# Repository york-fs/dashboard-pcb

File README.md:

# York FS Dashboard 
An embedded dashboard built around an STM32F103XX microcontroller with a 1920x480 LCD DWIN display for driver interaction and real time system status

## Features
- **Display**
  - 1920x480 DWIN TFT (https://www.dwin-global.com/8-88-inch-uart-smart-lcm-model-dmg19480c088_03w-product/)
  - Used for system feedback and driver information  
- **Controls**
  - 3-position illuminated rocker switch for *Ready to Drive* control  
- **Indicators**
  - 4 × 1 W high-power LEDs with dedicated PWM drivers  
  - Functions:  
    - IMD (Insulation Monitoring Device)  
    - BMS (Battery Management System)  
    - Ready to Drive  
    - TSAL (Traction System Active Light)  
- **Communication**
  - Integrated CAN transceiver  

## PCB Notes
- Designed in KiCad 9.0
- 3D models stored in external library (dashboard.pretty)

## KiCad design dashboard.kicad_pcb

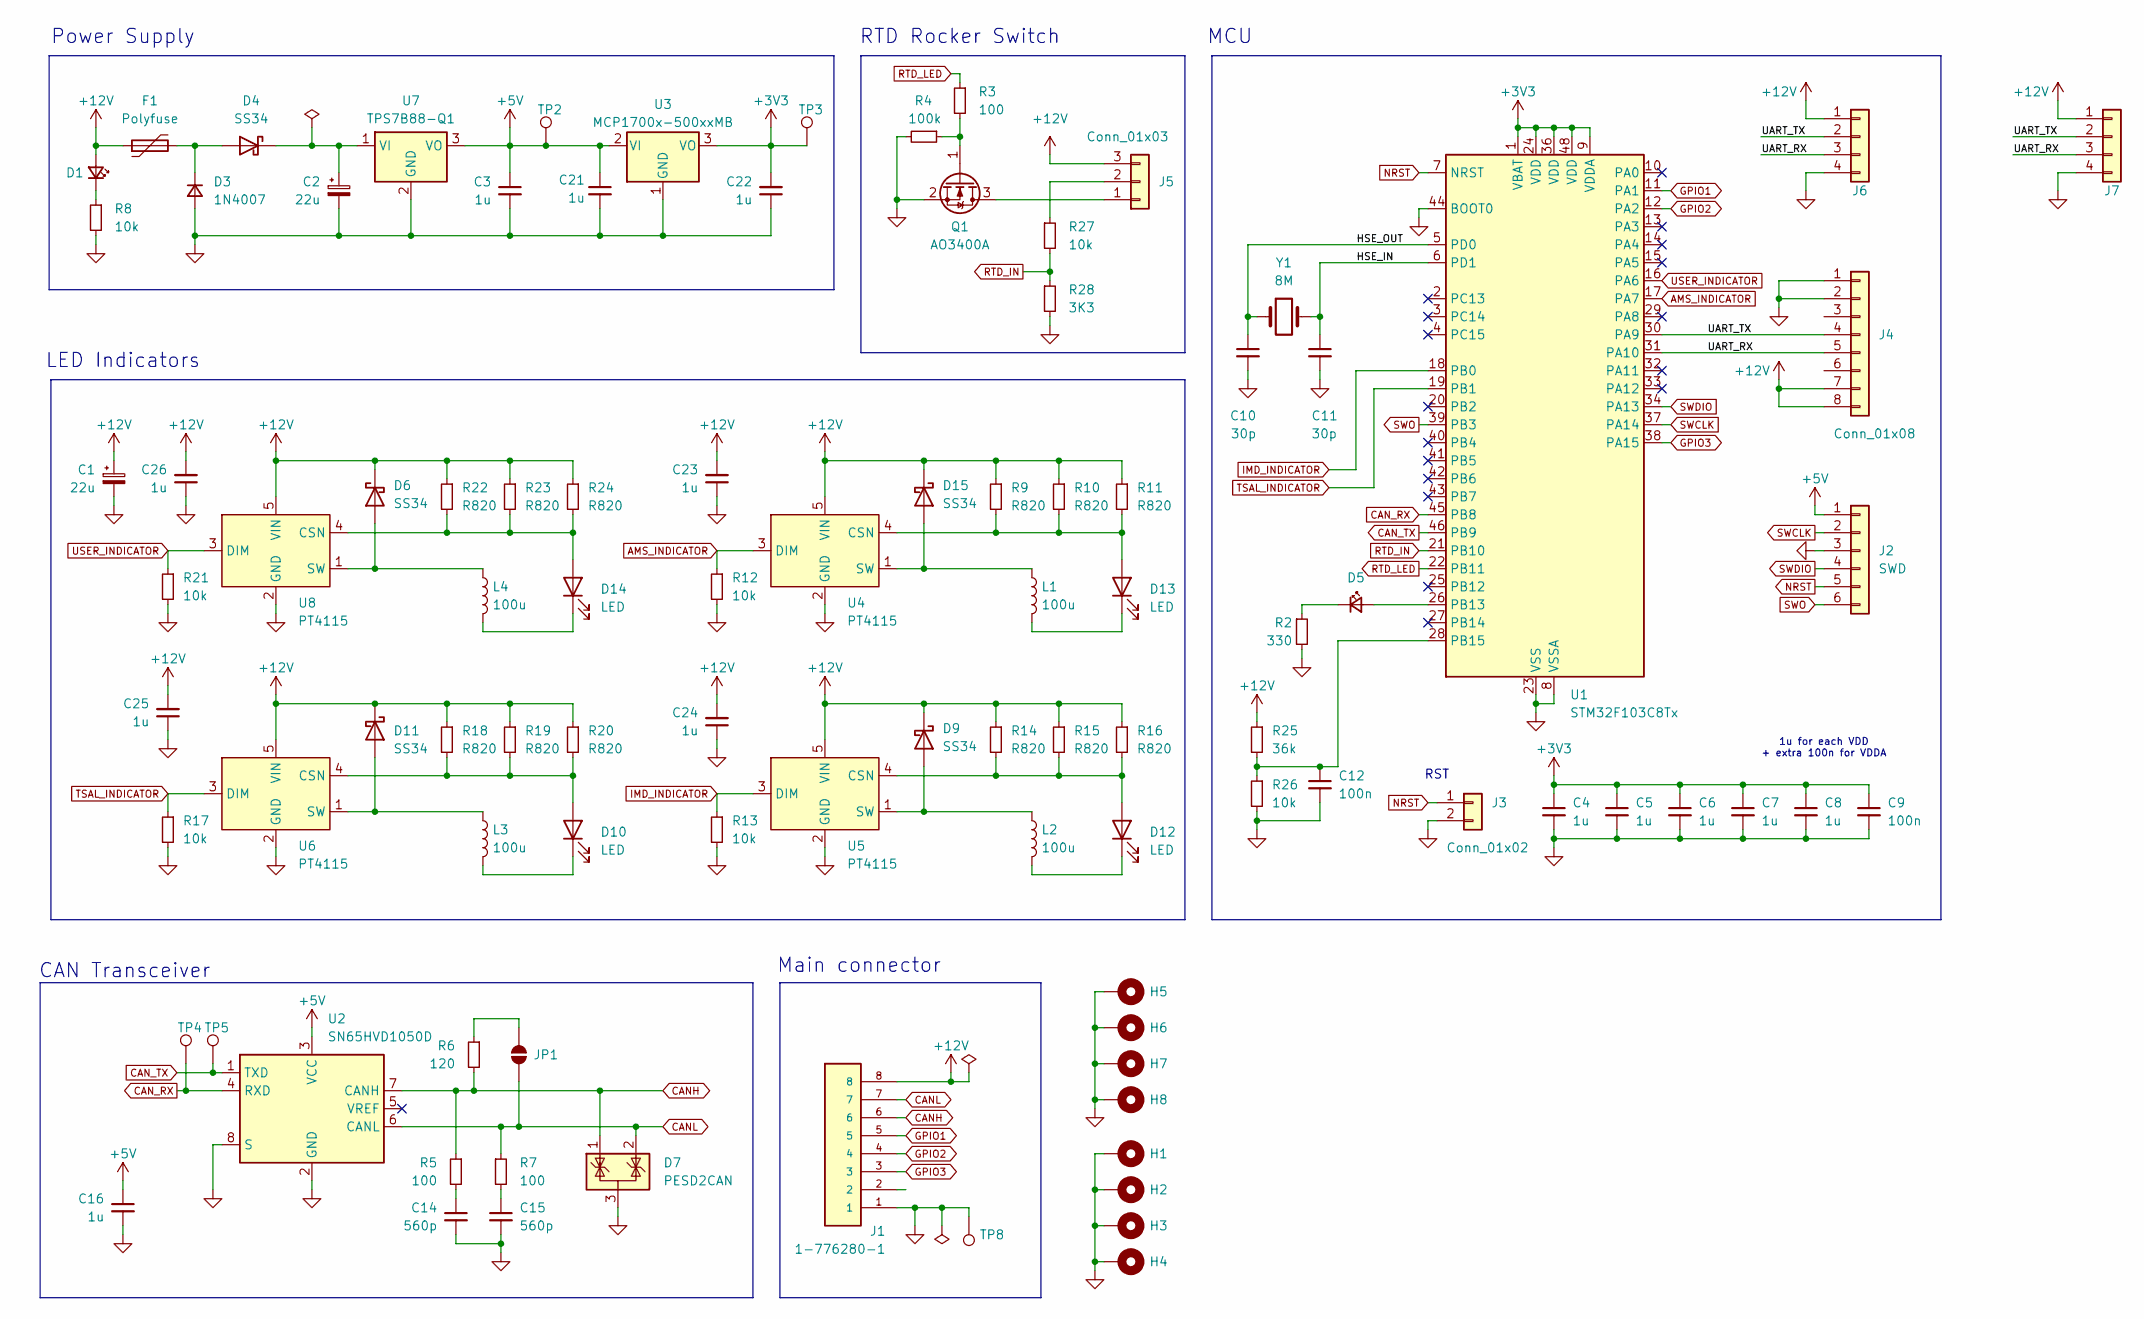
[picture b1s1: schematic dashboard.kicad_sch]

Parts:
C1, C2: 22u; CP_Elec_6.3x7.7; Mfr # EEEFK1J220XP
C3, C4, C5, C6, C7, C8, C16, C21, C22, C23, C24, C25, C26: 1u; C_0603_1608Metric
C9, C12: 100n; C_0603_1608Metric
C10, C11: 30p; C_0603_1608Metric
C14, C15: 560p; C_0603_1608Metric
D1, D5: LED_Small; LED_0603_1608Metric
D3: 1N4007; D_SOD-123F
D4, D6, D9, D11, D15: SS34; D_SMA
D7: PESD2CAN; SOT-23
D10, D12, D13, D14: LED; LED SMD 8x7.3mm; LCSC C5349974
F1: Polyfuse; R_0805_2012Metric
H1, H2, H3, H4: MountingHole_Pad; MountingHole_3.2mm_M3_Pad_Via
H5, H6, H7, H8: MountingHole_Pad; MountingHole_4.3mm_M4_Pad_Via
J1: 1-776280-1; TE_1-776275-1; PARTREV F8
J2: SWD; PinHeader_1x06_P2.54mm_Vertical
J3: Conn_01x02; PinHeader_1x02_P2.54mm_Vertical
J4: Conn_01x08; HY2-0-8PWT
J5: Conn_01x03; PinHeader_1x03_P2.54mm_Vertical
J6, J7: I2C; JST_PH_B4B-PH-K_1x04_P2.00mm_Vertical; Mfr # B4B-PH-K-S(LF)(SN)
JP1: SolderJumper_2_Open; SolderJumper-2_P1.3mm_Open_RoundedPad1.0x1.5mm
L1, L2, L3, L4: 100u; L_Chilisin_BMRF00101040
Q1: AO3400A; SOT-23
R2: 330; R_0603_1608Metric
R3, R5, R7: 100; R_0603_1608Metric
R4: 100k; R_0603_1608Metric
R6: 120; R_0603_1608Metric
R8, R12, R13, R17, R21, R26, R27: 10k; R_0603_1608Metric
R9, R10, R11, R14, R15, R16, R18, R19, R20, R22, R23, R24: R820; R_0603_1608Metric
R25: 36k; R_0603_1608Metric
R28: 3K3; R_0603_1608Metric
TP2, TP3, TP8: TestPoint; TestPoint_Pad_D2.0mm
TP4, TP5: TestPoint; TestPoint_Pad_D1.0mm
U1: STM32F103C8Tx; LQFP-48_7x7mm_P0.5mm
U2: SN65HVD1050D; SOIC-8_3.9x4.9mm_P1.27mm
U3: MCP1700x-500xxMB; SOT-89-3
U4, U5, U6, U8: PT4115; SOT-89-5
U7: TPS7B88-Q1; TO-252-2
Y1: 8M; Crystal_SMD_5032-2Pin_5.0x3.2mm

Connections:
+3V3: C4.1, C5.1, C6.1, C7.1, C8.1, C9.1, C22.2, TP3.1, U1.1 (VBAT), U1.9 (VDDA), U1.24 (VDD), U1.36 (VDD), U1.48 (VDD), U3.3 (VO)
+5V: C3.1, C16.1, C21.1, J2.1, TP2.1, U2.3 (VCC), U3.2 (VI), U7.3 (VO)
+12V: C1.1, C23.2, C24.2, C25.2, C26.2, D1.2 (A), D6.1 (K), D9.1 (K), D11.1 (K), D15.1 (K), F1.1, J1.8, J4.7, J4.8, J5.3, J6.1, J7.1, R9.1, R10.1, R11.1, R14.1, R15.1, R16.1, R18.1, R19.1, R20.1, R22.1, R23.1, R24.1, R25.1, U4.5 (VIN), U5.5 (VIN), U6.5 (VIN), U8.5 (VIN)
/HSE_IN: C11.1, U1.6 (PD1), Y1.2
/HSE_OUT: C10.1, U1.5 (PD0), Y1.1
/UART_RX: J4.5, J6.3, J7.3, U1.31 (PA10)
/UART_TX: J4.4, J6.2, J7.2, U1.30 (PA9)
AMS_INDICATOR: R12.1, U1.17 (PA7), U4.3 (DIM)
CANH: D7.1 (K), J1.6, R5.1, R6.2, U2.7 (CANH)
CANL: D7.2 (K), J1.7, JP1.2 (B), R7.1, U2.6 (CANL)
CAN_RX: TP4.1, U1.45 (PB8), U2.4 (RXD)
CAN_TX: TP5.1, U1.46 (PB9), U2.1 (TXD)
GND: C1.2, C2.2, C3.2, C4.2, C5.2, C6.2, C7.2, C8.2, C9.2, C10.2, C11.2, C12.2, C14.2, C15.2, C16.2, C21.2, C22.1, C23.1, C24.1, C25.1, C26.1, D3.2 (A), D7.3 (A), H1.1, H2.1, H3.1, H4.1, H5.1, H6.1, H7.1, H8.1, J1.1, J2.3, J3.2, J4.1, J4.2, J6.4, J7.4, Q1.2 (S), R2.2, R4.2, R8.2, R12.2, R13.2, R17.2, R21.2, R26.2, R28.2, TP8.1, U1.8 (VSSA), U1.23 (VSS), U1.35 (VSS), U1.44 (BOOT0), U1.47 (VSS), U2.2 (GND), U2.8 (S), U3.1 (GND), U4.2 (GND), U5.2 (GND), U6.2 (GND), U7.2 (GND), U8.2 (GND)
GPIO1: J1.5, U1.11 (PA1)
GPIO2: J1.4, U1.12 (PA2)
GPIO3: J1.3, U1.38 (PA15)
IMD_INDICATOR: R13.1, U1.18 (PB0), U5.3 (DIM)
NRST: J2.5, J3.1, U1.7 (NRST)
unnamed: C14.1, R5.2
unnamed: C15.1, R7.2
unnamed: D1.1 (K), R8.1
unnamed: D3.1 (K), D4.2 (A), F1.2
unnamed: C2.1, D4.1 (K), U7.1 (VI)
unnamed: D5.2 (A), U1.26 (PB13)
unnamed: D5.1 (K), R2.1
unnamed: D6.2 (A), L4.1, U8.1 (SW)
unnamed: D9.2 (A), L2.1, U5.1 (SW)
unnamed: D10.2 (A), R18.2, R19.2, R20.2, U6.4 (CSN)
unnamed: D10.1 (K), L3.2
unnamed: D11.2 (A), L3.1, U6.1 (SW)
unnamed: D12.2 (A), R14.2, R15.2, R16.2, U5.4 (CSN)
unnamed: D12.1 (K), L2.2
unnamed: D13.2 (A), R9.2, R10.2, R11.2, U4.4 (CSN)
unnamed: D13.1 (K), L1.2
unnamed: D14.2 (A), R22.2, R23.2, R24.2, U8.4 (CSN)
unnamed: D14.1 (K), L4.2
unnamed: D15.2 (A), L1.1, U4.1 (SW)
unnamed: J5.1, Q1.3 (D)
unnamed: J5.2, R27.1
unnamed: JP1.1 (A), R6.1
unnamed: Q1.1 (G), R3.2, R4.1
unnamed: C12.1, R25.2, R26.1, U1.28 (PB15)
RTD_IN: R27.2, R28.1, U1.21 (PB10)
RTD_LED: R3.1, U1.22 (PB11)
SWCLK: J2.2, U1.37 (PA14)
SWDIO: J2.4, U1.34 (PA13)
SWO: J2.6, U1.39 (PB3)
TSAL_INDICATOR: R17.1, U1.19 (PB1), U6.3 (DIM)
USER_INDICATOR: R21.1, U1.16 (PA6), U8.3 (DIM)

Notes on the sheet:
LED Indicators
1u for each VDD + extra 100n for VDDA
Power Supply
Main connector
RTD Rocker Switch
RST
MCU
CAN Transceiver

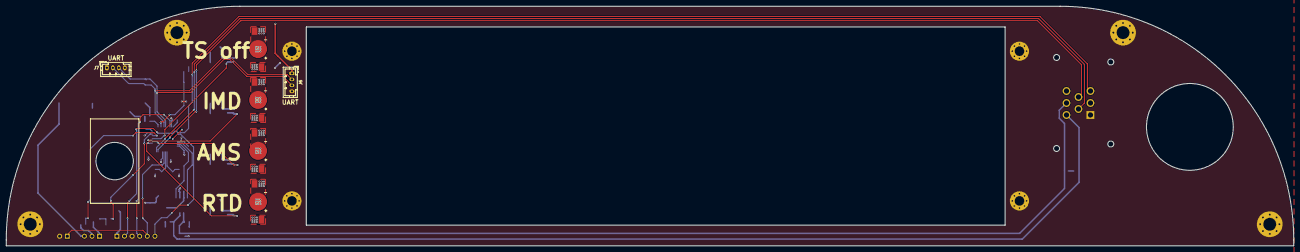
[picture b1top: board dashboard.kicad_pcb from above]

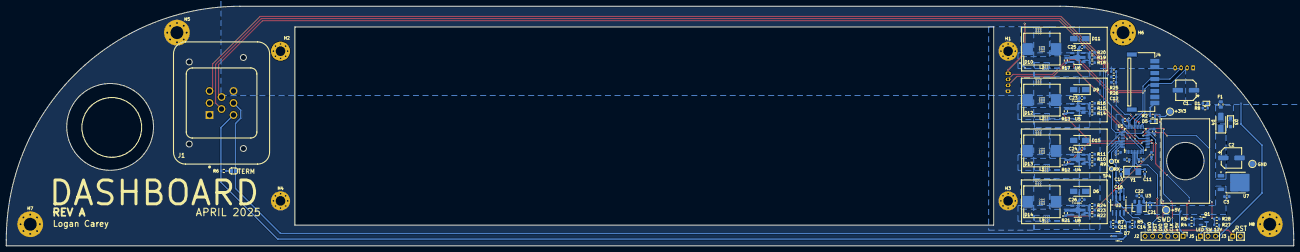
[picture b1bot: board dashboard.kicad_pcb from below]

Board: 2 copper layers, 430.0 x 80.0 mm, 97 parts (83 on the bottom side), 49 nets.

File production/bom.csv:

Designator,Footprint,Quantity,Value,LCSC Part #
"C1, C2",CP_Elec_6.3x7.7,2,22u,
"C10, C11",0603,2,30p,
"C12, C9",0603,2,100n,
"C14, C15",0603,2,560p,
"C16, C21, C22, C23, C24, C25, C26, C3, C4, C5, C6, C7, C8",0603,13,1u,
"D1, D5",0603,2,LED_Small,
"D10, D12, D13, D14",LED SMD 8x7.3mm,4,LED,C5349974
"D11, D15, D4, D6, D9",D_SMA,5,SS34,
D3,D_SOD-123F,1,1N4007,
D7,SOT-23,1,PESD2CAN,
F1,0805,1,Polyfuse,
"H1, H2, H3, H4",MountingHole_3.2mm_M3_Pad_Via,4,MountingHole_Pad,
"H5, H6, H7, H8",MountingHole_4.3mm_M4_Pad_Via,4,MountingHole_Pad,
J1,TE_1-776275-1,1,1-776280-1,
J2,PinHeader_1x06_P2.54mm_Vertical,1,SWD,
J3,PinHeader_1x02_P2.54mm_Vertical,1,Conn_01x02,
J4,HY2-0-8PWT,1,Conn_01x08,
J5,PinHeader_1x03_P2.54mm_Vertical,1,Conn_01x03,
"J6, J7",JST_PH_B4B-PH-K_1x04_P2.00mm_Vertical,2,I2C,
JP1,SolderJumper-2_P1.3mm_Open_RoundedPad1.0x1.5mm,1,SolderJumper_2_Open,
"L1, L2, L3, L4",L_Chilisin_BMRF00101040,4,100u,
Q1,SOT-23,1,AO3400A,
"R10, R11, R14, R15, R16, R18, R19, R20, R22, R23, R24, R9",0603,12,R820,
"R12, R13, R17, R21, R26, R27, R8",0603,7,10k,
R2,0603,1,330,
R25,0603,1,36k,
R28,0603,1,3K3,
"R3, R5, R7",0603,3,100,
R4,0603,1,100k,
R6,0603,1,120,
"TP2, TP3, TP8",TestPoint_Pad_D2.0mm,3,TestPoint,
"TP4, TP5",TestPoint_Pad_D1.0mm,2,TestPoint,
U1,LQFP-48_7x7mm_P0.5mm,1,STM32F103C8Tx,
U2,SOIC-8_3.9x4.9mm_P1.27mm,1,SN65HVD1050D,
U3,SOT-89-3,1,MCP1700x-500xxMB,
"U4, U5, U6, U8",SOT-89-5,4,PT4115,
U7,TO-252-2,1,TPS7B88-Q1,
Y1,Crystal_SMD_5032-2Pin_5.0x3.2mm,1,8M,

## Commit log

2025-09-24 Revison A
2025-09-24 Rev A Production files
